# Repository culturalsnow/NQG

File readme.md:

# NQG: Not Quite Gherkin

NQG (Not Quite Gherkin) is a 30% ortholinear keyboard with a macro key and dedicated row for thumb keys, made by emptystring studio.

Keyboard Maintainer: [Cultural Snow](https://github.com/culturalsnow)/[SA_EndlessGame](http://twitter.com/SA_EndlessGame)  
Hardware Supported: NQG PCB, Pro Micro  
Hardware Availability: Kits are available from [SA_EndlessGame](http://twitter.com/SA_EndlessGame)  

Make example for this keyboard (after setting up your build environment):

    make NQG:default

See the [build environment setup](https://docs.qmk.fm/#/getting_started_build_tools) and the [make instructions](https://docs.qmk.fm/#/getting_started_make_guide) for more information. Brand new to QMK? Start with our [Complete Newbs Guide](https://docs.qmk.fm/#/newbs).

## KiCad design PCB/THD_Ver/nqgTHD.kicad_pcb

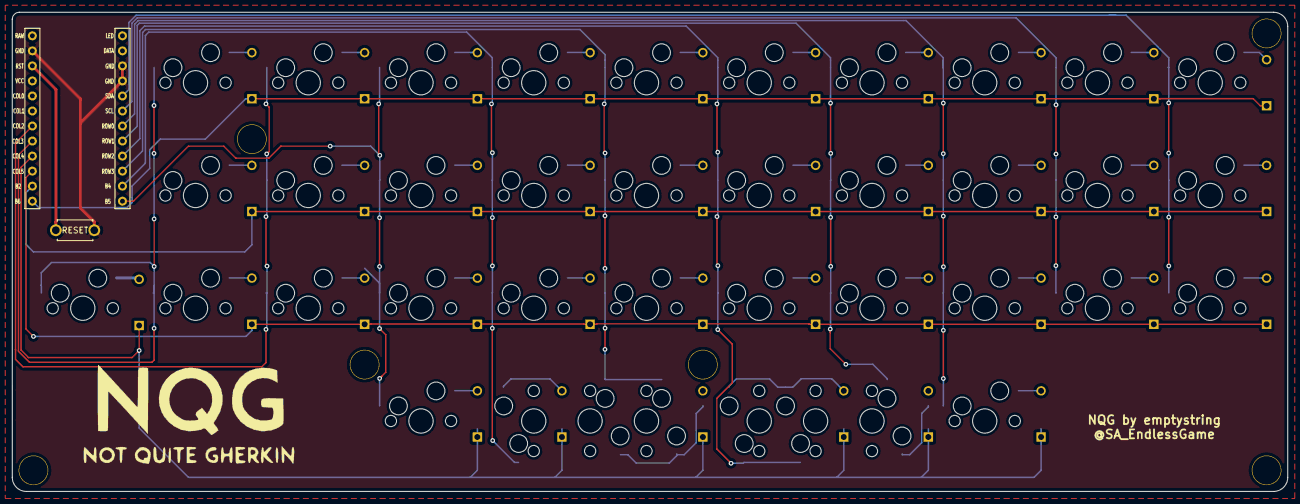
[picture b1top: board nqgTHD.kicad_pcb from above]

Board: 2 copper layers, 215.5 x 81.0 mm, 84 parts (0 on the bottom side), 53 nets.

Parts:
D1, D2, D3, D4, D5, D6, D7, D8, D9, D10, D11, D12, D13, D14, D15, D16, D17, D18, D19, D20, D21, D22, D23, D24, D25, D26, D27, D28, D29, D30, D31, D32, D33, D34, D35, D36, D37: D; Diode-Hybrid-Back
Ref**: Val**; HOLE
Ref**#2, Ref**#3, Ref**#4, Ref**#5, Ref**#6: Val**; HOLE
SW1, SW2, SW3, SW4, SW5, SW6, SW7, SW8, SW9, SW10, SW11, SW12, SW13, SW14, SW15, SW16, SW17, SW18, SW19, SW20, SW21, SW22, SW23, SW24, SW25, SW26, SW27, SW28, SW29, SW30, SW31, SW32, SW33, SW34, SW35, SW36, SW37, SW38, SW39: SW_PUSH; CherryMX_Hotswap_Back
SW40: SW_PUSH; ResetSW
U1: ProMicro; ProMicro_v2_Backside

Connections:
GND: SW40.1, U1.3, U1.4, U1.23
unnamed: D1.2, SW1.2
unnamed: D2.2, SW2.2
unnamed: D3.2, SW3.2
unnamed: D4.2, SW4.2
unnamed: D5.2, SW5.2
unnamed: D6.2, SW6.2
unnamed: D7.2, SW7.2
unnamed: D8.2, SW8.2
unnamed: D9.2, SW9.2
unnamed: D10.2, SW10.2
unnamed: D11.2, SW11.2
unnamed: D12.2, SW12.2
unnamed: D13.2, SW13.2
unnamed: D14.2, SW14.2
unnamed: D15.2, SW15.2
unnamed: D16.2, SW16.2
unnamed: D17.2, SW17.2
unnamed: D18.2, SW18.2
unnamed: D19.2, SW19.2, SW38.2
unnamed: D20.2, SW20.2
unnamed: D21.2, SW21.2
unnamed: D22.2, SW22.2
unnamed: D23.2, SW23.2, SW39.2
unnamed: D24.2, SW24.2
unnamed: D25.2, SW25.2
unnamed: D26.2, SW26.2
unnamed: D27.2, SW27.2
unnamed: D28.2, SW28.2
unnamed: D29.2, SW29.2
unnamed: D30.2, SW30.2
unnamed: D31.2, SW31.2
unnamed: D32.2, SW32.2
unnamed: D33.2, SW33.2
unnamed: D34.2, SW34.2
unnamed: D35.2, SW35.2
unnamed: D36.2, SW36.2
unnamed: D37.2, SW37.2
col0: SW1.1, SW2.1, SW3.1, SW4.1, U1.17
col1: SW5.1, SW6.1, SW7.1, U1.18
col2: SW8.1, SW9.1, SW10.1, SW11.1, U1.12
col3: SW12.1, SW13.1, SW14.1, SW15.1, U1.11
col4: SW16.1, SW17.1, SW18.1, SW19.1, SW38.1, U1.10
col5: SW20.1, SW21.1, SW22.1, SW23.1, SW39.1, U1.9
col6: SW24.1, SW25.1, SW26.1, SW27.1, U1.8
col7: SW28.1, SW29.1, SW30.1, SW31.1, U1.7
col8: SW32.1, SW33.1, SW34.1, U1.6
col9: SW35.1, SW36.1, SW37.1, U1.5
reset: SW40.2, U1.22
row0: D1.1, D5.1, D8.1, D12.1, D16.1, D20.1, D24.1, D28.1, D32.1, D35.1, U1.13
row1: D2.1, D6.1, D9.1, D13.1, D17.1, D21.1, D25.1, D29.1, D33.1, D36.1, U1.14
row2: D3.1, D7.1, D10.1, D14.1, D18.1, D22.1, D26.1, D30.1, D34.1, D37.1, U1.15
row3: D4.1, D11.1, D15.1, D19.1, D23.1, D27.1, D31.1, U1.16

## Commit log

2019-03-16 first push 20190317
2019-03-16 added mounting holes
2019-03-17 rounded edges
2019-03-18 added gerber zip
2019-03-19 new dxf for plate added
2019-03-20 rerouted, larger holes, plates
2019-03-25 firmware in progress
2019-03-25 redid wiring, firmware halfway done
2019-03-25 new image
2019-03-28 working firmware 20190328
2019-03-29 updated keymap
2019-03-29 updated keymap 20190329
2019-03-30 beta pcb added
2019-04-02 new keymap
2019-04-05 fixed up files for pull request
2019-04-21 added THD version, removed beta_01
2019-04-21 now switch # matches up with diode # in SMD version as well
2019-06-08 added new screw to THD version, created new plates with new screw locations
2019-06-16 images for build guide
2019-06-16 build guide first draft
2019-06-16 build guide update
